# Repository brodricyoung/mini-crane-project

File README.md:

# Mini Crane Project

This repository contains the documentation and resources for my Mini Crane project, completed as part of my Individual Technical Project for professional career preparation. The project demonstrates a crane system controlled by an STM32 Nucleo microcontroller, with sensors and manual controls for crane motion and hook manipulation.

---

## 📄 Project Report

The full project report PDF is available here:

*(download for best experience navigating and for links)*

[Mini Crane Project Report](https://github.com/brodricyoung/mini-crane-project/blob/main/Documentation/Mini_Crane_Project_Report.pdf)

---

## 🖼 Images

Images of the crane assembly, components, and system setup, and schematics are included in the `images` folder:

[Images](./Documentation/images/)

---

## 🎥 Project Demo Video

Watch the project in action so far on YouTube:

[Mini Crane Demo #1](https://youtu.be/VVNfatb6yKk)

---

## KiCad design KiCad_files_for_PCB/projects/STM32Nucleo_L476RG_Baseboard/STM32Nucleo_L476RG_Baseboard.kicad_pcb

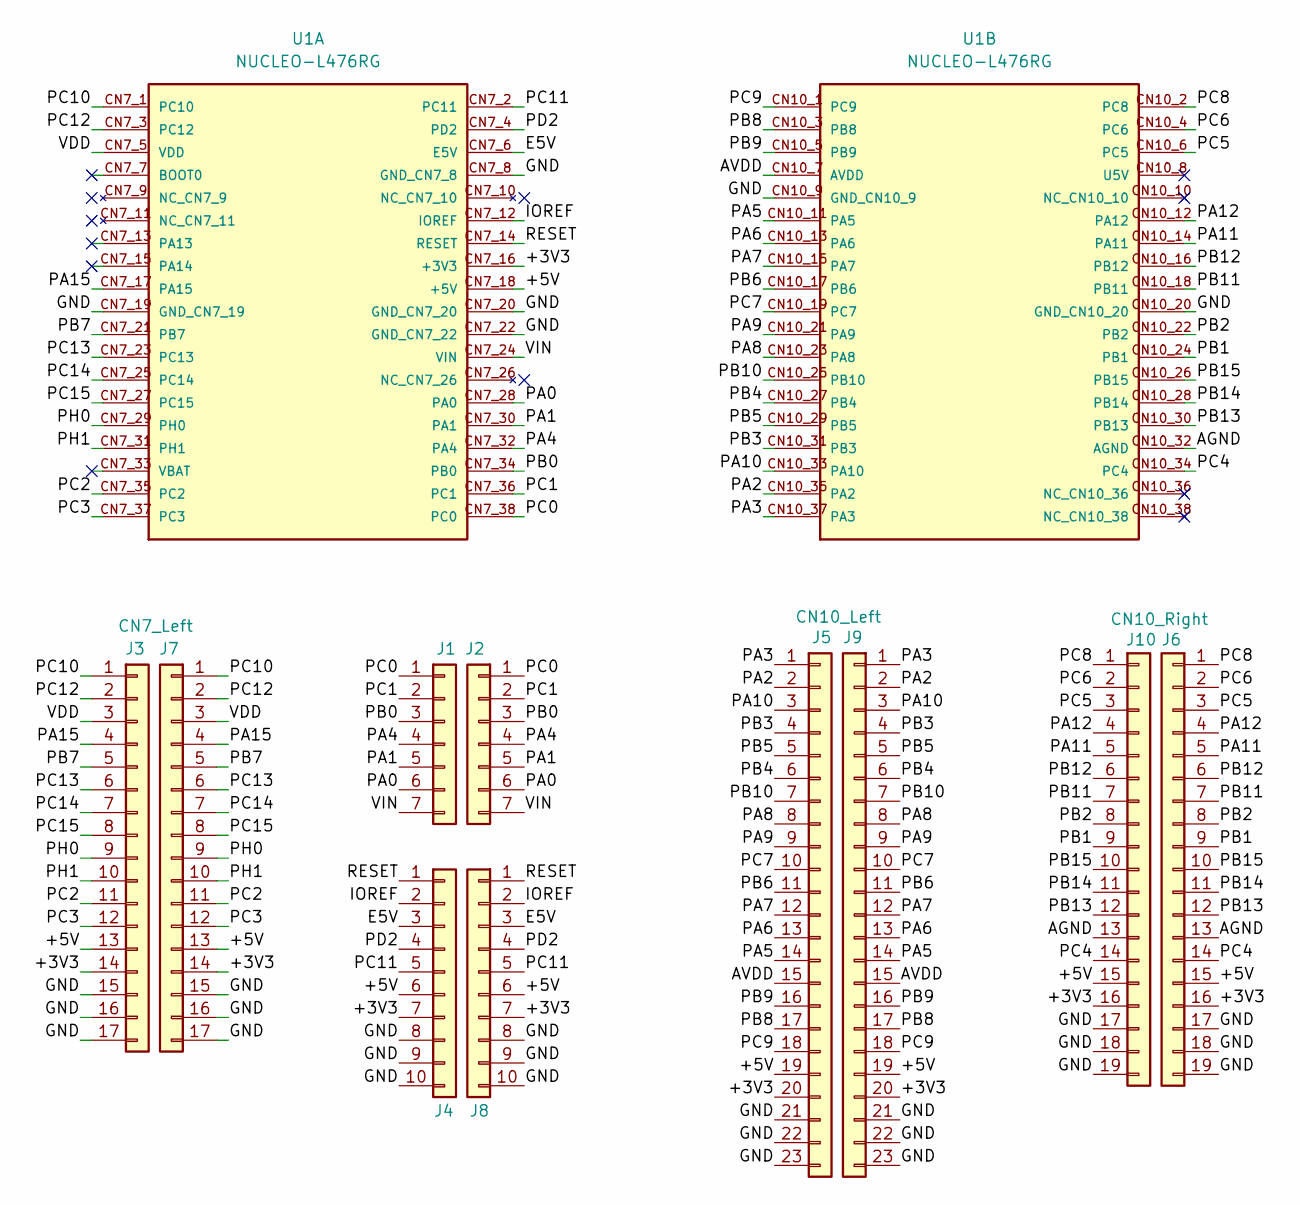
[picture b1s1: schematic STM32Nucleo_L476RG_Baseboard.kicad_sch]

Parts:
J1: Conn_01x07; PinSocket_1x07_P2.54mm_Vertical
J2: Conn_01x07; PinHeader_1x07_P2.54mm_Vertical
J3: CN7_Left; PinHeader_1x17_P2.54mm_Vertical
J4: Conn_01x10; PinSocket_1x10_P2.54mm_Vertical
J5: CN10_Left; PinHeader_1x23_P2.54mm_Vertical
J6: CN10_Right; PinHeader_1x19_P2.54mm_Vertical
J7: CN7_Left; PinSocket_1x17_P2.54mm_Vertical
J8: Conn_01x10; PinHeader_1x10_P2.54mm_Vertical
J9: CN10_Left; PinSocket_1x23_P2.54mm_Vertical
J10: CN10_Right; PinSocket_1x19_P2.54mm_Vertical
U1: NUCLEO-L476RG; MODULE_NUCLEO-L476RG; PARTREV 15

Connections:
/+3V3: J3.14, J4.7, J5.20, J6.16, J7.14, J8.7, J9.20, J10.16, U1.CN7_16 (+3V3)
/+5V: J3.13, J4.6, J5.19, J6.15, J7.13, J8.6, J9.19, J10.15, U1.CN7_18 (+5V)
/AGND: J6.13, J10.13, U1.CN10_32 (AGND)
/AVDD: J5.15, J9.15, U1.CN10_7 (AVDD)
/E5V: J4.3, J8.3, U1.CN7_6 (E5V)
/GND: J3.15, J3.16, J3.17, J4.8, J4.9, J4.10, J5.21, J5.22, J5.23, J6.17, J6.18, J6.19, J7.15, J7.16, J7.17, J8.8, J8.9, J8.10, J9.21, J9.22, J9.23, J10.17, J10.18, J10.19, U1.CN7_8 (GND_CN7_8), U1.CN7_19 (GND_CN7_19), U1.CN7_20 (GND_CN7_20), U1.CN7_22 (GND_CN7_22), U1.CN10_9 (GND_CN10_9), U1.CN10_20 (GND_CN10_20)
/IOREF: J4.2, J8.2, U1.CN7_12 (IOREF)
/PA0: J1.6, J2.6, U1.CN7_28 (PA0)
/PA1: J1.5, J2.5, U1.CN7_30 (PA1)
/PA2: J5.2, J9.2, U1.CN10_35 (PA2)
/PA3: J5.1, J9.1, U1.CN10_37 (PA3)
/PA4: J1.4, J2.4, U1.CN7_32 (PA4)
/PA5: J5.14, J9.14, U1.CN10_11 (PA5)
/PA6: J5.13, J9.13, U1.CN10_13 (PA6)
/PA7: J5.12, J9.12, U1.CN10_15 (PA7)
/PA8: J5.8, J9.8, U1.CN10_23 (PA8)
/PA9: J5.9, J9.9, U1.CN10_21 (PA9)
/PA10: J5.3, J9.3, U1.CN10_33 (PA10)
/PA11: J6.5, J10.5, U1.CN10_14 (PA11)
/PA12: J6.4, J10.4, U1.CN10_12 (PA12)
/PA15: J3.4, J7.4, U1.CN7_17 (PA15)
/PB0: J1.3, J2.3, U1.CN7_34 (PB0)
/PB1: J6.9, J10.9, U1.CN10_24 (PB1)
/PB2: J6.8, J10.8, U1.CN10_22 (PB2)
/PB3: J5.4, J9.4, U1.CN10_31 (PB3)
/PB4: J5.6, J9.6, U1.CN10_27 (PB4)
/PB5: J5.5, J9.5, U1.CN10_29 (PB5)
/PB6: J5.11, J9.11, U1.CN10_17 (PB6)
/PB7: J3.5, J7.5, U1.CN7_21 (PB7)
/PB8: J5.17, J9.17, U1.CN10_3 (PB8)
/PB9: J5.16, J9.16, U1.CN10_5 (PB9)
/PB10: J5.7, J9.7, U1.CN10_25 (PB10)
/PB11: J6.7, J10.7, U1.CN10_18 (PB11)
/PB12: J6.6, J10.6, U1.CN10_16 (PB12)
/PB13: J6.12, J10.12, U1.CN10_30 (PB13)
/PB14: J6.11, J10.11, U1.CN10_28 (PB14)
/PB15: J6.10, J10.10, U1.CN10_26 (PB15)
/PC0: J1.1, J2.1, U1.CN7_38 (PC0)
/PC1: J1.2, J2.2, U1.CN7_36 (PC1)
/PC2: J3.11, J7.11, U1.CN7_35 (PC2)
/PC3: J3.12, J7.12, U1.CN7_37 (PC3)
/PC4: J6.14, J10.14, U1.CN10_34 (PC4)
/PC5: J6.3, J10.3, U1.CN10_6 (PC5)
/PC6: J6.2, J10.2, U1.CN10_4 (PC6)
/PC7: J5.10, J9.10, U1.CN10_19 (PC7)
/PC8: J6.1, J10.1, U1.CN10_2 (PC8)
/PC9: J5.18, J9.18, U1.CN10_1 (PC9)
/PC10: J3.1, J7.1, U1.CN7_1 (PC10)
/PC11: J4.5, J8.5, U1.CN7_2 (PC11)
/PC12: J3.2, J7.2, U1.CN7_3 (PC12)
/PC13: J3.6, J7.6, U1.CN7_23 (PC13)
/PC14: J3.7, J7.7, U1.CN7_25 (PC14)
/PC15: J3.8, J7.8, U1.CN7_27 (PC15)
/PD2: J4.4, J8.4, U1.CN7_4 (PD2)
/PH0: J3.9, J7.9, U1.CN7_29 (PH0)
/PH1: J3.10, J7.10, U1.CN7_31 (PH1)
/RESET: J4.1, J8.1, U1.CN7_14 (RESET)
/VDD: J3.3, J7.3, U1.CN7_5 (VDD)
/VIN: J1.7, J2.7, U1.CN7_24 (VIN)

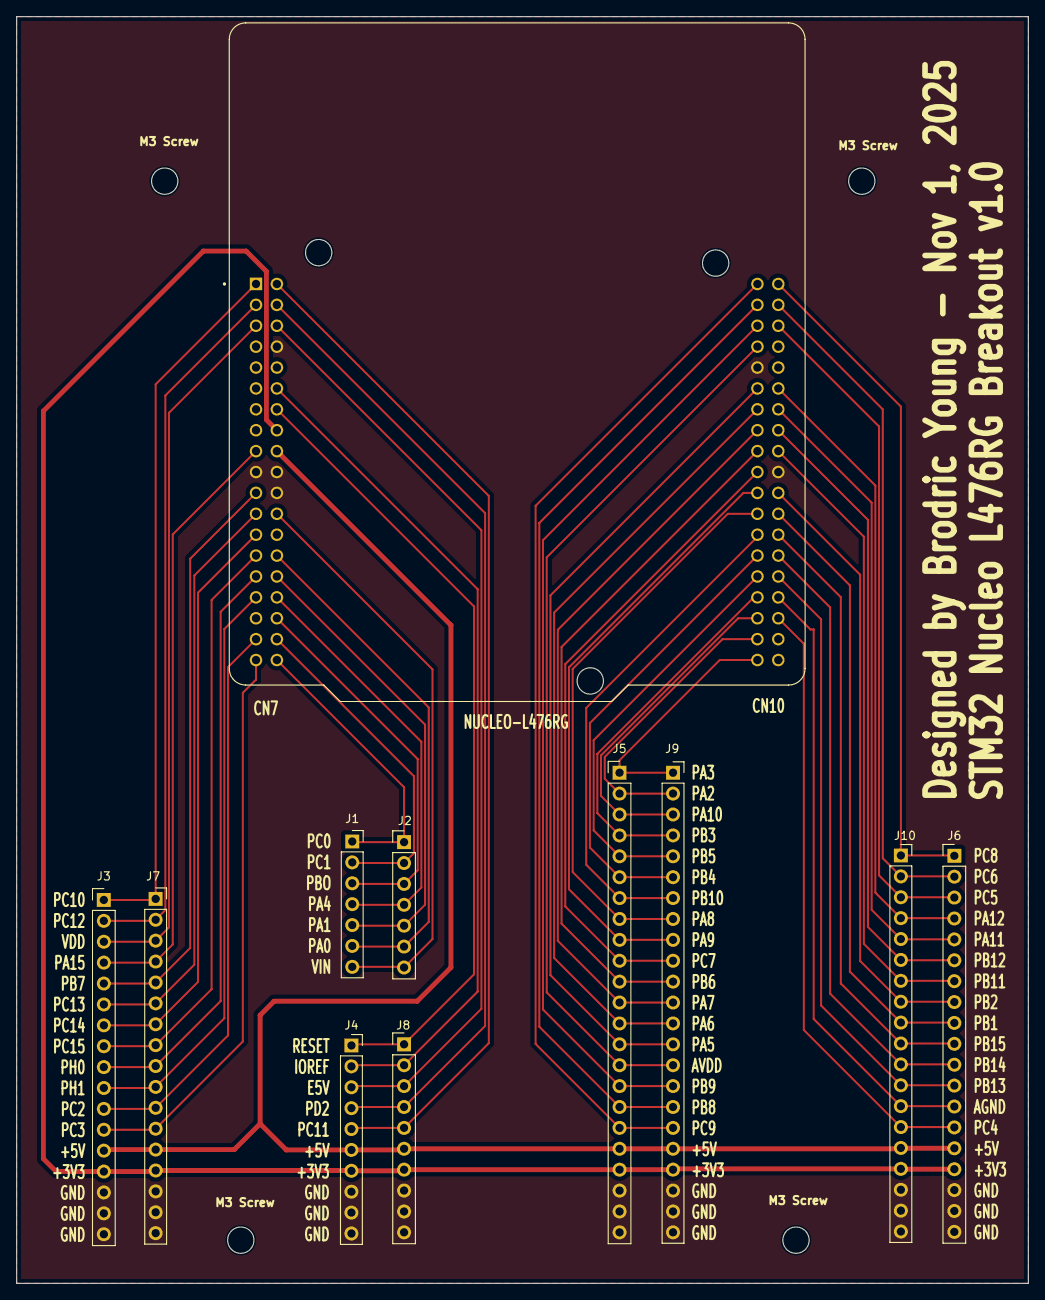
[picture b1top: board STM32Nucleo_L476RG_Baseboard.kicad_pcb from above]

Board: 2 copper layers, 123.0 x 154.0 mm, 11 parts (0 on the bottom side), 59 nets.

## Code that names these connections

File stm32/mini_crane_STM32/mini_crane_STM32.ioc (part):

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Mcu.Name=STM32L476R(C-E-G)Tx
Mcu.Package=LQFP64
Mcu.UserName=STM32L476RGTx
PA0.GPIOParameters=GPIO_Label
PA0.GPIO_Label=RotaryEncoder_CLK
PA0.Signal=S_TIM2_CH1
PA1.GPIOParameters=GPIO_Label
PA1.GPIO_Label=RotaryEncoder_DT
PA1.Signal=S_TIM2_CH2
PA11.GPIOParameters=GPIO_Speed,GPIO_Label
PA11.GPIO_Label=Slew_IN3
PA11.GPIO_Speed=GPIO_SPEED_FREQ_LOW
PA11.Signal=GPIO_Output
PA12.GPIOParameters=GPIO_Label
PA12.GPIO_Label=Slew_IN4
PA12.Signal=GPIO_Output
PA13\ (JTMS-SWDIO).GPIOParameters=GPIO_Label
PA13\ (JTMS-SWDIO).GPIO_Label=TMS
PA13\ (JTMS-SWDIO).Mode=Serial_Wire
PA13\ (JTMS-SWDIO).Signal=SYS_JTMS-SWDIO
PA14\ (JTCK-SWCLK).GPIOParameters=GPIO_Label
PA14\ (JTCK-SWCLK).GPIO_Label=TCK
PA14\ (JTCK-SWCLK).Mode=Serial_Wire
PA14\ (JTCK-SWCLK).Signal=SYS_JTCK-SWCLK
PA2.GPIOParameters=GPIO_Speed,GPIO_PuPd,GPIO_Label,GPIO_Mode
PA2.GPIO_Label=USART_TX
PA2.GPIO_Mode=GPIO_MODE_AF_PP
PA2.GPIO_PuPd=GPIO_NOPULL
PA2.GPIO_Speed=GPIO_SPEED_FREQ_VERY_HIGH
PA2.Mode=Asynchronous
PA2.Signal=USART2_TX
PA3.GPIOParameters=GPIO_Speed,GPIO_PuPd,GPIO_Label,GPIO_Mode
PA3.GPIO_Label=USART_RX
PA3.GPIO_Mode=GPIO_MODE_AF_PP
PA3.GPIO_PuPd=GPIO_NOPULL
PA3.GPIO_Speed=GPIO_SPEED_FREQ_VERY_HIGH
PA3.Mode=Asynchronous
PA3.Signal=USART2_RX
PA5.GPIOParameters=GPIO_Speed,GPIO_PuPd,GPIO_Label,GPIO_ModeDefaultOutputPP
PA5.GPIO_Label=LD2 [green Led]
PA5.GPIO_ModeDefaultOutputPP=GPIO_MODE_OUTPUT_PP
PA5.GPIO_PuPd=GPIO_NOPULL
PA5.GPIO_Speed=GPIO_SPEED_FREQ_LOW
PA5.Signal=GPIO_Output
PA6.GPIOParameters=GPIO_Label
PA6.GPIO_Label=Winch_IN1
PA6.Signal=GPIO_Output
PA7.GPIOParameters=GPIO_Label
PA7.GPIO_Label=Winch_IN2
PA7.Signal=GPIO_Output
PA8.GPIOParameters=GPIO_Label
PA8.GPIO_Label=Trolley_IN3
PA8.Signal=GPIO_Output
PA9.GPIOParameters=GPIO_Label
PA9.GPIO_Label=Trolley_IN4
PA9.Signal=GPIO_Output
PB0.GPIOParameters=GPIO_PuPd,GPIO_Label,GPIO_ModeDefaultEXTI
PB0.GPIO_Label=RotaryEncoder_SW
PB0.GPIO_ModeDefaultEXTI=GPIO_MODE_IT_FALLING
PB0.GPIO_PuPd=GPIO_PULLUP
PB0.Signal=GPXTI0
PB1.GPIOParameters=GPIO_Label
PB1.GPIO_Label=Slew_IN1
PB1.Signal=GPIO_Output
PB10.Mode=Asynchronous
PB10.Signal=USART3_TX
PB11.Mode=Asynchronous
PB11.Signal=USART3_RX
PB2.GPIOParameters=GPIO_Label
PB2.GPIO_Label=Slew_IN2
PB2.Signal=GPIO_Output
PB3\ (JTDO-TRACESWO).GPIOParameters=GPIO_Label
PB3\ (JTDO-TRACESWO).GPIO_Label=SWO
PB3\ (JTDO-TRACESWO).Signal=SYS_JTDO-SWO
PB8.GPIOParameters=GPIO_Pu
PB8.GPIO_Pu=GPIO_PULLUP
PB8.Mode=I2C
PB8.Signal=I2C1_SCL
PB9.GPIOParameters=GPIO_Pu
PB9.GPIO_Pu=GPIO_PULLUP
PB9.Mode=I2C
PB9.Signal=I2C1_SDA
PC13.GPIOParameters=GPIO_PuPd,GPIO_Label,GPIO_ModeDefaultEXTI
PC13.GPIO_Label=B1 [Blue PushButton]
PC13.GPIO_ModeDefaultEXTI=GPIO_MODE_IT_FALLING
PC13.GPIO_PuPd=GPIO_NOPULL
PC13.Signal=GPXTI13
PC14-OSC32_IN\ (PC14).Mode=LSE-External-Oscillator
PC14-OSC32_IN\ (PC14).Signal=RCC_OSC32_IN
PC15-OSC32_OUT\ (PC15).Mode=LSE-External-Oscillator
PC15-OSC32_OUT\ (PC15).Signal=RCC_OSC32_OUT
PH0-OSC_IN\ (PH0).Signal=RCC_OSC_IN
PH1-OSC_OUT\ (PH1).Signal=RCC_OSC_OUT
RCC.HSE_VALUE=8000000
RCC.SYSCLKFreq_VALUE=80000000
RCC.SYSCLKSource=RCC_SYSCLKSOURCE_PLLCLK
board=NUCLEO-L476RG
boardIOC=true

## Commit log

2025-12-17 first documentation, pcb files
2025-12-17 more images
2025-12-17 pcb images
2025-12-17 project report
2025-12-17 report navigation
